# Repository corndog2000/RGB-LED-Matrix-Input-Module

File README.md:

# RGB-LED-Matrix-Input-Module

# Please check this project's license. It uses a Attribution-NonCommercial-ShareAlike 4.0 International license.

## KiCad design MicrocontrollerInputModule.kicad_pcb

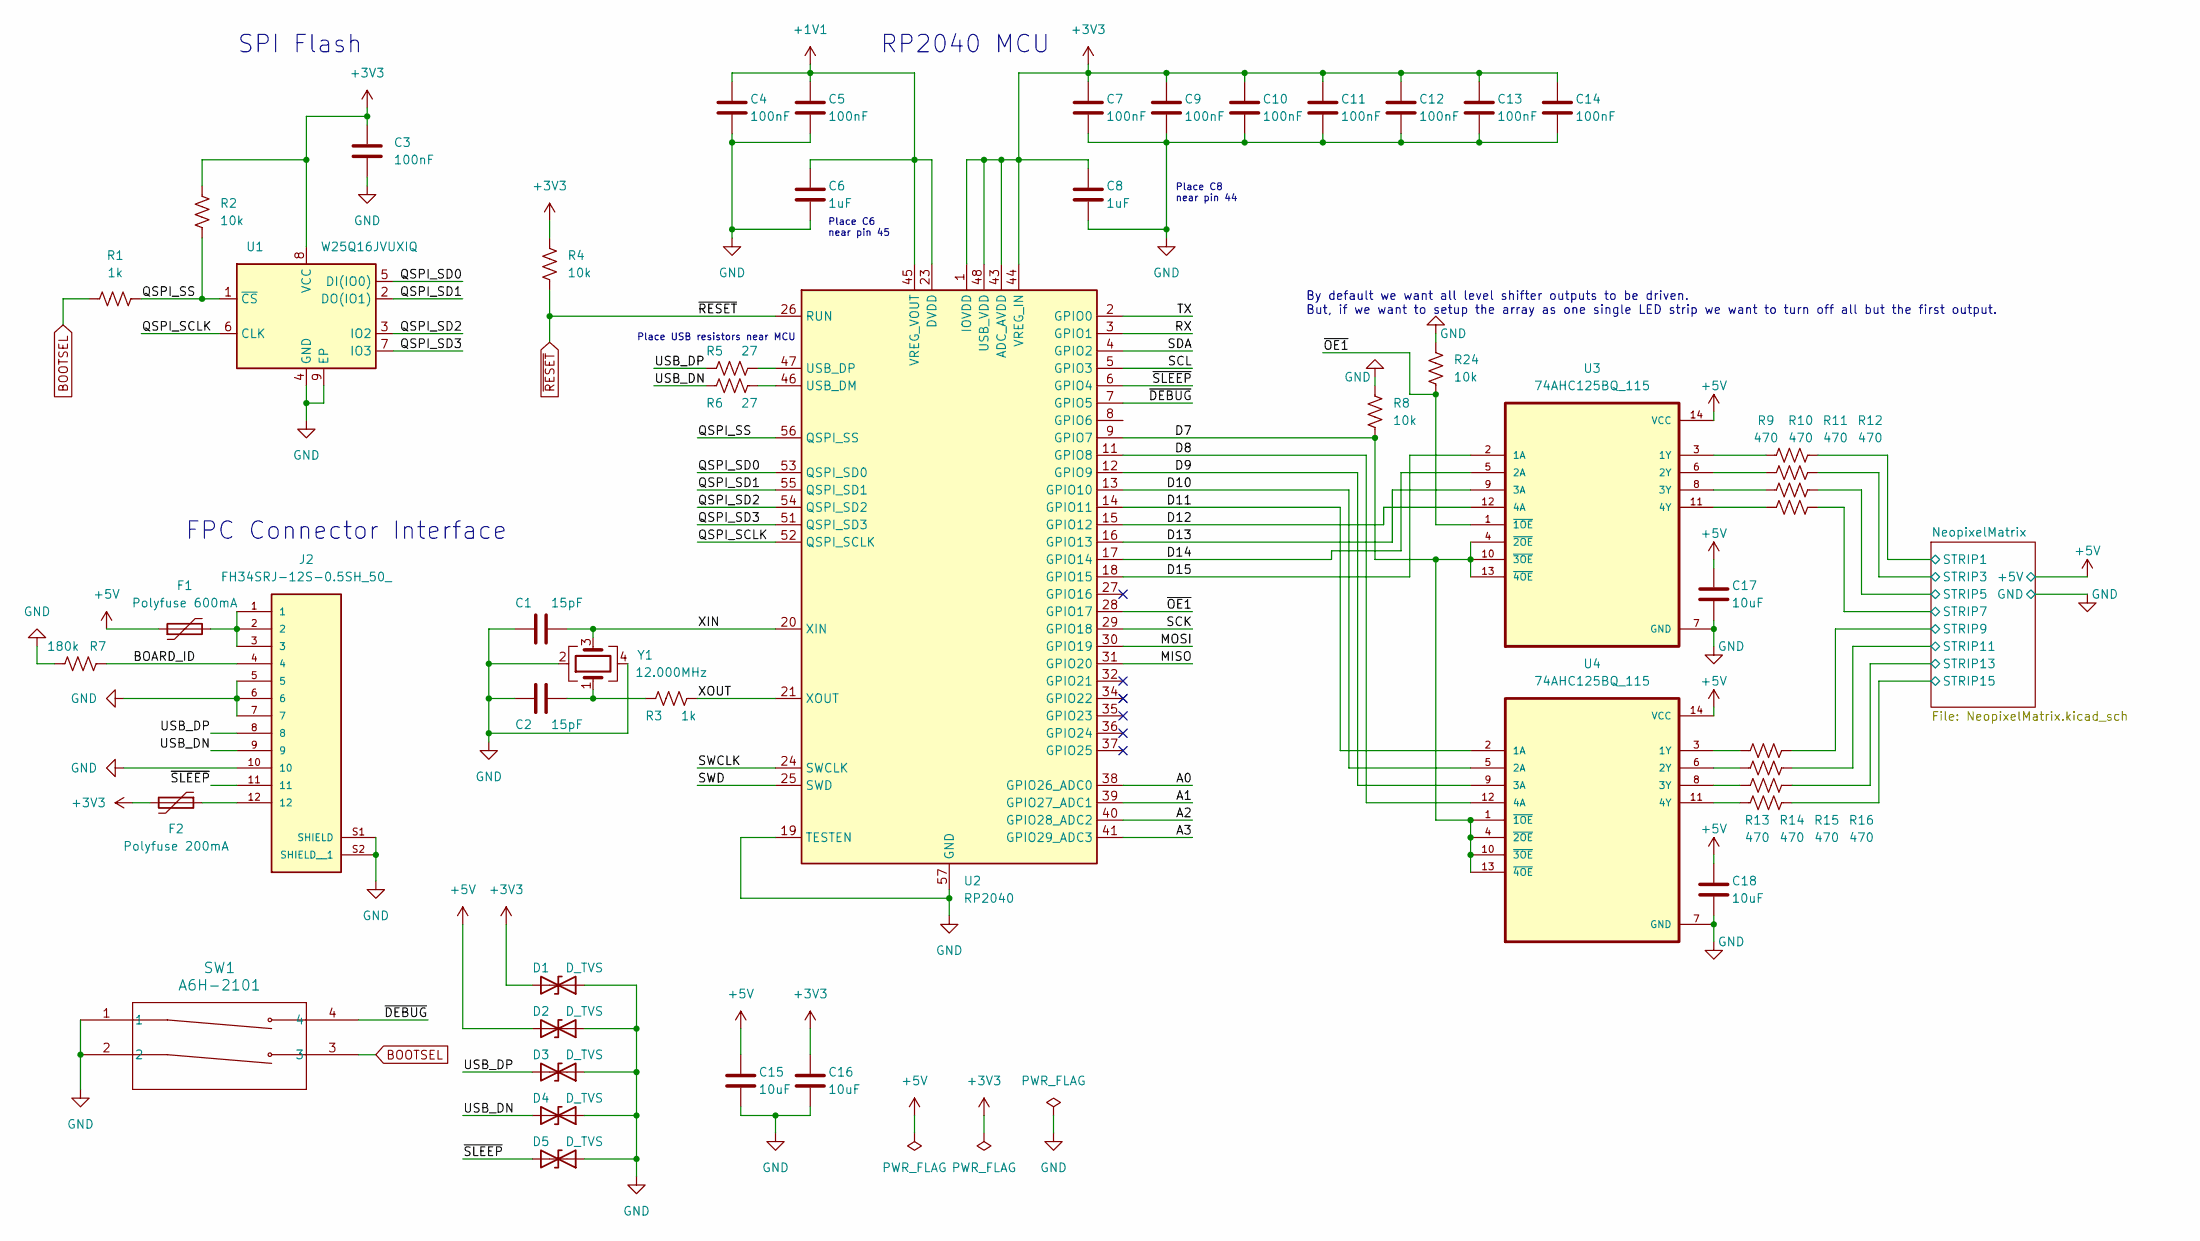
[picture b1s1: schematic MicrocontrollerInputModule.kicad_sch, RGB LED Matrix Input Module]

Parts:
C1, C2: 15pF; C_0402_1005Metric; LCSC Part # C76950
C3, C4, C5, C7, C9, C10, C11, C12, C13, C14: 100nF; C_0402_1005Metric; LCSC Part # C1525
C6, C8: 1uF; C_0402_1005Metric; LCSC Part # C29266
C15, C16, C17, C18: 10uF; C_0603_1608Metric; LCSC Part # C19702
D1, D2, D3, D4, D5: D_TVS; D_0402_1005Metric; LCSC Part # C468904
F1: Polyfuse 600mA; R_1206_3216Metric; LCSC Part # C883122
F2: Polyfuse 200mA; R_1206_3216Metric; LCSC Part # C910826
J2: FH34SRJ-12S-0.5SH_50_; HRS_FH34SRJ-12S-0.5SH_50_; LCSC Part # C424659
R1, R3: 1k; R_0402_1005Metric; LCSC Part # C106235
R2, R4, R8, R24: 10k; R_0402_1005Metric; LCSC Part # C60490
R5, R6: 27; R_0402_1005Metric; LCSC Part # C138021
R7: 180k; R_0402_1005Metric; LCSC Part # C138046
R9, R10, R11, R12, R13, R14, R15, R16: 470; R_0402_1005Metric; LCSC Part # C25117
SW1: A6H-2101; SW_A6H-2101_OMR; LCSC Part # C224990
U1: W25Q16JVUXIQ; SON-8-1EP_3x2mm_P0.5mm_EP0.2x1.6mm; LCSC Part # C2843335
U2: RP2040; QFN-56-1EP_7x7mm_P0.4mm_EP3.2x3.2mm; LCSC Part # C2040
U3, U4: 74AHC125BQ_115; QFN50P300X250X100-15N; LCSC Part # C554218
Y1: 12.000MHz; Crystal_SMD_3225-4Pin_3.2x2.5mm; LCSC Part # C7294551

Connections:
+1V1: C4.1, C5.1, C6.1, U2.23 (DVDD), U2.45 (VREG_VOUT), U2.50 (DVDD)
+3V3: C3.1, C7.1, C8.1, C9.1, C10.1, C11.1, C12.1, C13.1, C14.1, C16.1, D1.2 (A2), F2.2, R2.1, R4.1, U1.8 (VCC), U2.1 (IOVDD), U2.10 (IOVDD), U2.22 (IOVDD), U2.33 (IOVDD), U2.42 (IOVDD), U2.43 (ADC_AVDD), U2.44 (VREG_IN), U2.48 (USB_VDD), U2.49 (IOVDD)
+5V: C15.1, C17.1, C18.1, D2.2 (A2), F1.1, U3.14 (VCC), U4.14 (VCC); also elsewhere on the board
/A0: U2.38 (GPIO26_ADC0)
/A1: U2.39 (GPIO27_ADC1)
/A2: U2.40 (GPIO28_ADC2)
/A3: U2.41 (GPIO29_ADC3)
/BOARD_ID: J2.4, R7.1
/D7: R8.2, U2.9 (GPIO7), U3.4 (~2OE), U3.10 (~3OE), U3.13 (~4OE), U4.1 (~1OE), U4.4 (~2OE), U4.10 (~3OE), U4.13 (~4OE)
/D8: U2.11 (GPIO8), U4.12 (4A)
/D9: U2.12 (GPIO9), U4.9 (3A)
/D10: U2.13 (GPIO10), U4.5 (2A)
/D11: U2.14 (GPIO11), U4.2 (1A)
/D12: U2.15 (GPIO12), U3.12 (4A)
/D13: U2.16 (GPIO13), U3.9 (3A)
/D14: U2.17 (GPIO14), U3.5 (2A)
/D15: U2.18 (GPIO15), U3.2 (1A)
/MISO: U2.31 (GPIO20)
/MOSI: U2.30 (GPIO19)
/NeopixelMatrix/STRIP1: R9.2; also elsewhere on the board
/NeopixelMatrix/STRIP3: R10.2; also elsewhere on the board
/NeopixelMatrix/STRIP5: R11.2; also elsewhere on the board
/NeopixelMatrix/STRIP7: R12.2; also elsewhere on the board
/NeopixelMatrix/STRIP9: R13.2; also elsewhere on the board
/NeopixelMatrix/STRIP11: R14.2; also elsewhere on the board
/NeopixelMatrix/STRIP13: R15.2; also elsewhere on the board
/NeopixelMatrix/STRIP15: R16.2; also elsewhere on the board
/QSPI_SCLK: U1.6 (CLK), U2.52 (QSPI_SCLK)
/QSPI_SD0: U1.5 (DI(IO0)), U2.53 (QSPI_SD0)
/QSPI_SD1: U1.2 (DO(IO1)), U2.55 (QSPI_SD1)
/QSPI_SD2: U1.3 (IO2), U2.54 (QSPI_SD2)
/QSPI_SD3: U1.7 (IO3), U2.51 (QSPI_SD3)
/QSPI_SS: R1.2, R2.2, U1.1 (~CS), U2.56 (QSPI_SS)
/RX: U2.3 (GPIO1)
/SCK: U2.29 (GPIO18)
/SCL: U2.5 (GPIO3)
/SDA: U2.4 (GPIO2)
/SWCLK: U2.24 (SWCLK)
/SWD: U2.25 (SWD)
/TX: U2.2 (GPIO0)
/USB_DN: D4.2 (A2), J2.9, R6.1
/USB_DP: D3.2 (A2), J2.8, R5.1
/XIN: C1.2, U2.20 (XIN), Y1.3
/XOUT: R3.2, U2.21 (XOUT)
/~DEBUG: SW1.4, U2.7 (GPIO5)
/~OE1: R24.2, U2.28 (GPIO17), U3.1 (~1OE)
/~SLEEP: D5.2 (A2), J2.11, U2.6 (GPIO4)
BOOTSEL: R1.1, SW1.3
GND: C1.1, C2.1, C3.2, C4.2, C5.2, C6.2, C7.2, C8.2, C9.2, C10.2, C11.2, C12.2, C13.2, C14.2, C15.2, C16.2, C17.2, C18.2, D1.1 (A1), D2.1 (A1), D3.1 (A1), D4.1 (A1), D5.1 (A1), J2.5, J2.6, J2.7, J2.10, J2.S1 (SHIELD), J2.S2 (SHIELD__1), R7.2, R8.1, R24.1, SW1.1, SW1.2, U1.4 (GND), U1.9 (EP), U2.19 (TESTEN), U2.57 (GND), U3.7 (GND), U4.7 (GND), Y1.2, Y1.4; also elsewhere on the board
unnamed: C2.2, R3.1, Y1.1
unnamed: F1.2, J2.1, J2.2, J2.3
unnamed: F2.1, J2.12
unnamed: R6.2, U2.46 (USB_DM)
unnamed: R5.2, U2.47 (USB_DP)
unnamed: R9.1, U3.3 (1Y)
unnamed: R10.1, U3.6 (2Y)
unnamed: R11.1, U3.8 (3Y)
unnamed: R12.1, U3.11 (4Y)
unnamed: R13.1, U4.3 (1Y)
unnamed: R14.1, U4.6 (2Y)
unnamed: R15.1, U4.8 (3Y)
unnamed: R16.1, U4.11 (4Y)
~RESET: R4.2, U2.26 (RUN)

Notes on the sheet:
By default we want all level shifter outputs to be driven. But, if we want to setup the array as one single LED strip we want to turn off all but the first output.
SPI Flash
Place C8 near pin 44
Place USB resistors near MCU
Place C6 near pin 45
FPC Connector Interface
RP2040 MCU

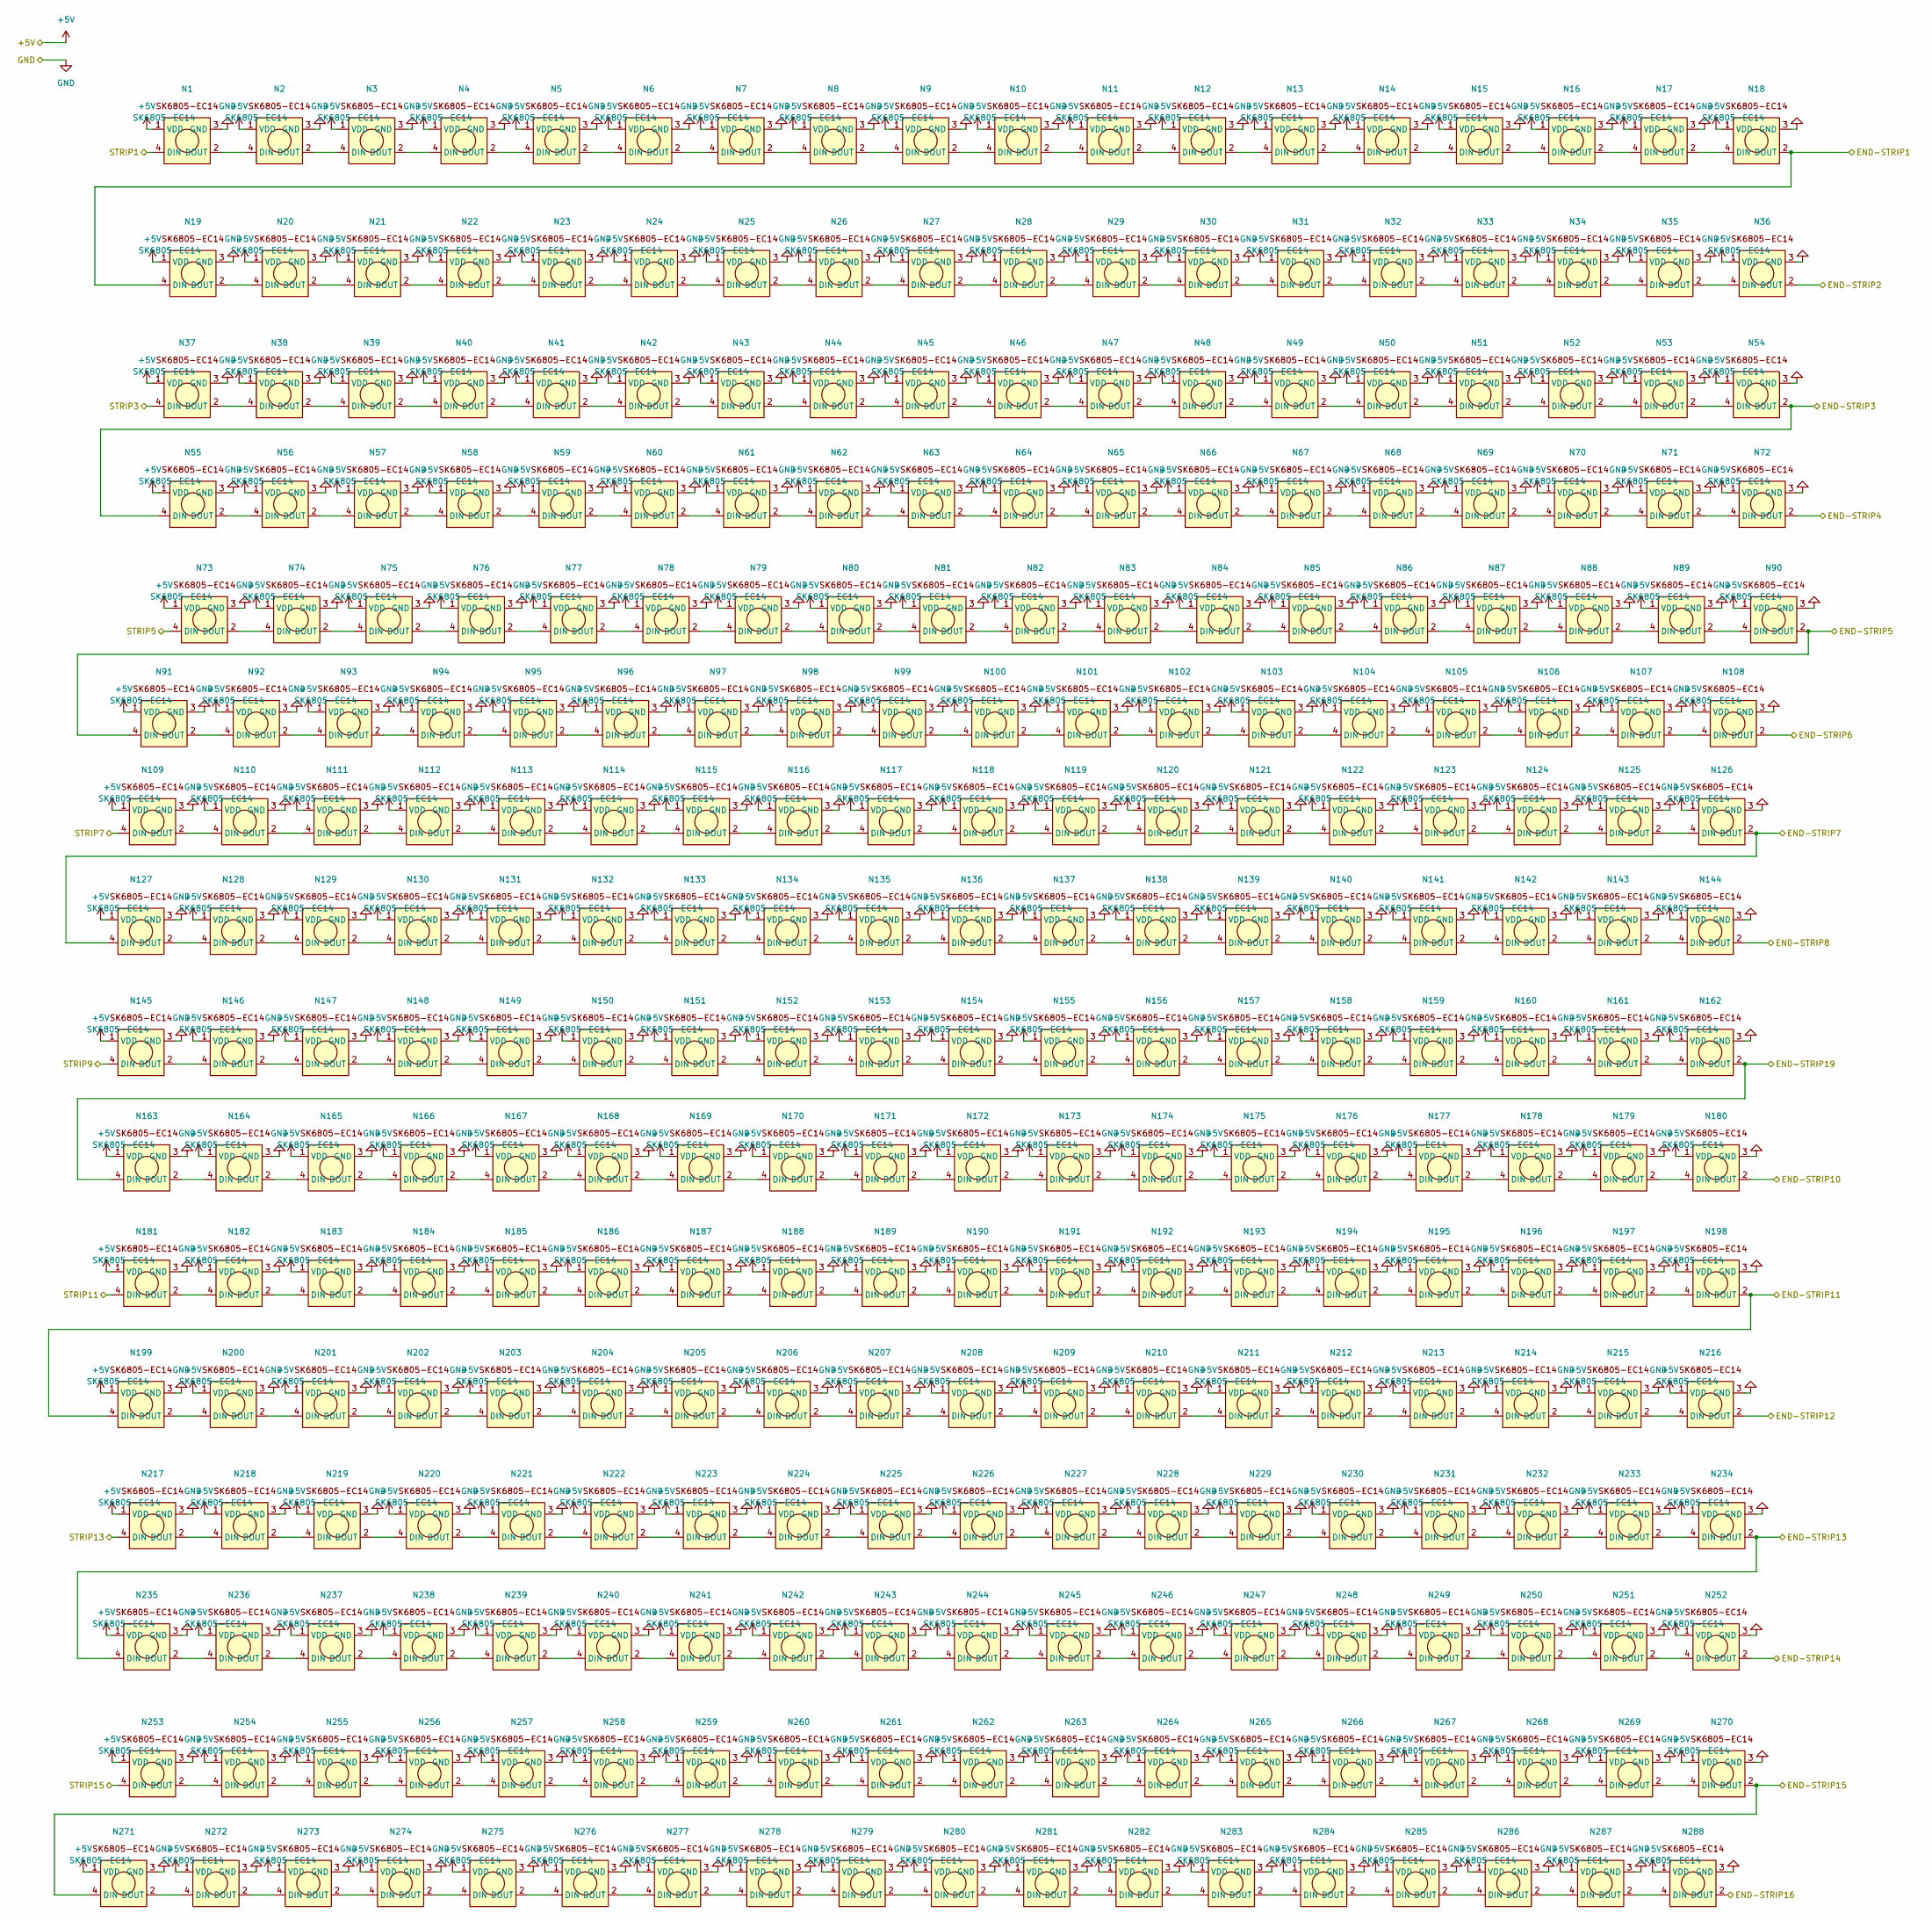
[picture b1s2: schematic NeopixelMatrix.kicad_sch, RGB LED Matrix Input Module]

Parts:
N1, N2, N3, N4, N5, N6, N7, N8, N9, N10, N11, N12, N13, N14, N15, N16, N17, N18, N19, N20, N21, N22, N23, N24, N25, N26, N27, N28, N29, N30, N31, N32, N33, N34, N35, N36, N37, N38, N39, N40, N41, N42, N43, N44, N45, N46, N47, N48, N49, N50, N51, N52, N53, N54, N55, N56, N57, N58, N59, N60, N61, N62, N63, N64, N65, N66, N67, N68, N69, N70, N71, N72, N73, N74, N75, N76, N77, N78, N79, N80, N81, N82, N83, N84, N85, N86, N87, N88, N89, N90, N91, N92, N93, N94, N95, N96, N97, N98, N99, N100, N101, N102, N103, N104, N105, N106, N107, N108, N109, N110, N111, N112, N113, N114, N115, N116, N117, N118, N119, N120, N121, N122, N123, N124, N125, N126, N127, N128, N129, N130, N131, N132, N133, N134, N135, N136, N137, N138, N139, N140, N141, N142, N143, N144, N145, N146, N147, N148, N149, N150, N151, N152, N153, N154, N155, N156, N157, N158, N159, N160, N161, N162, N163, N164, N165, N166, N167, N168, N169, N170, N171, N172, N173, N174, N175, N176, N177, N178, N179, N180, N181, N182, N183, N184, N185, N186, N187, N188, N189, N190, N191, N192, N193, N194, N195, N196, N197, N198, N199, N200, N201, N202, N203, N204, N205, N206, N207, N208, N209, N210, N211, N212, N213, N214, N215, N216, N217, N218, N219, N220, N221, N222, N223, N224, N225, N226, N227, N228, N229, N230, N231, N232, N233, N234, N235, N236, N237, N238, N239, N240, N241, N242, N243, N244, N245, N246, N247, N248, N249, N250, N251, N252, N253, N254, N255, N256, N257, N258, N259, N260, N261, N262, N263, N264, N265, N266, N267, N268, N269, N270, N271, N272, N273, N274, N275, N276, N277, N278, N279, N280, N281, N282, N283, N284, N285, N286, N287, N288: SK6805-EC14; LCSC Part # C2909055

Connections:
+5V: N1.1 (VDD), N2.1 (VDD), N3.1 (VDD), N4.1 (VDD), N5.1 (VDD), N6.1 (VDD), N7.1 (VDD), N8.1 (VDD), N9.1 (VDD), N10.1 (VDD), N11.1 (VDD), N12.1 (VDD), N13.1 (VDD), N14.1 (VDD), N15.1 (VDD), N16.1 (VDD), N17.1 (VDD), N18.1 (VDD), N19.1 (VDD), N20.1 (VDD), N21.1 (VDD), N22.1 (VDD), N23.1 (VDD), N24.1 (VDD), N25.1 (VDD), N26.1 (VDD), N27.1 (VDD), N28.1 (VDD), N29.1 (VDD), N30.1 (VDD), N31.1 (VDD), N32.1 (VDD), N33.1 (VDD), N34.1 (VDD), N35.1 (VDD), N36.1 (VDD), N37.1 (VDD), N38.1 (VDD), N39.1 (VDD), N40.1 (VDD), N41.1 (VDD), N42.1 (VDD), N43.1 (VDD), N44.1 (VDD), N45.1 (VDD), N46.1 (VDD), N47.1 (VDD), N48.1 (VDD), N49.1 (VDD), N50.1 (VDD), N51.1 (VDD), N52.1 (VDD), N53.1 (VDD), N54.1 (VDD), N55.1 (VDD), N56.1 (VDD), N57.1 (VDD), N58.1 (VDD), N59.1 (VDD), N60.1 (VDD), N61.1 (VDD), N62.1 (VDD), N63.1 (VDD), N64.1 (VDD), N65.1 (VDD), N66.1 (VDD), N67.1 (VDD), N68.1 (VDD), N69.1 (VDD), N70.1 (VDD), N71.1 (VDD), N72.1 (VDD), N73.1 (VDD), N74.1 (VDD), N75.1 (VDD), N76.1 (VDD), N77.1 (VDD), N78.1 (VDD), N79.1 (VDD), N80.1 (VDD), N81.1 (VDD), N82.1 (VDD), N83.1 (VDD), N84.1 (VDD), N85.1 (VDD), N86.1 (VDD), N87.1 (VDD), N88.1 (VDD), N89.1 (VDD), N90.1 (VDD), N91.1 (VDD), N92.1 (VDD), N93.1 (VDD), N94.1 (VDD), N95.1 (VDD), N96.1 (VDD), N97.1 (VDD), N98.1 (VDD), N99.1 (VDD), N100.1 (VDD), N101.1 (VDD), N102.1 (VDD), N103.1 (VDD), N104.1 (VDD), N105.1 (VDD), N106.1 (VDD), N107.1 (VDD), N108.1 (VDD), N109.1 (VDD), N110.1 (VDD), N111.1 (VDD), N112.1 (VDD), N113.1 (VDD), N114.1 (VDD), N115.1 (VDD), N116.1 (VDD), N117.1 (VDD), N118.1 (VDD), N119.1 (VDD), N120.1 (VDD), N121.1 (VDD), N122.1 (VDD), N123.1 (VDD), N124.1 (VDD), N125.1 (VDD), N126.1 (VDD), N127.1 (VDD), N128.1 (VDD), N129.1 (VDD), N130.1 (VDD), N131.1 (VDD), N132.1 (VDD), N133.1 (VDD), N134.1 (VDD), N135.1 (VDD), N136.1 (VDD), N137.1 (VDD), N138.1 (VDD), N139.1 (VDD), N140.1 (VDD), N141.1 (VDD), N142.1 (VDD), N143.1 (VDD), N144.1 (VDD), N145.1 (VDD), N146.1 (VDD), N147.1 (VDD), N148.1 (VDD), N149.1 (VDD), N150.1 (VDD), N151.1 (VDD), N152.1 (VDD), N153.1 (VDD), N154.1 (VDD), N155.1 (VDD), N156.1 (VDD), N157.1 (VDD), N158.1 (VDD), N159.1 (VDD), N160.1 (VDD), N161.1 (VDD), N162.1 (VDD), N163.1 (VDD), N164.1 (VDD), N165.1 (VDD), N166.1 (VDD), N167.1 (VDD), N168.1 (VDD), N169.1 (VDD), N170.1 (VDD), N171.1 (VDD), N172.1 (VDD), N173.1 (VDD), N174.1 (VDD), N175.1 (VDD), N176.1 (VDD), N177.1 (VDD), N178.1 (VDD), N179.1 (VDD), N180.1 (VDD), N181.1 (VDD), N182.1 (VDD), N183.1 (VDD), N184.1 (VDD), N185.1 (VDD), N186.1 (VDD), N187.1 (VDD), N188.1 (VDD), N189.1 (VDD), N190.1 (VDD), N191.1 (VDD), N192.1 (VDD), N193.1 (VDD), N194.1 (VDD), N195.1 (VDD), N196.1 (VDD), N197.1 (VDD), N198.1 (VDD), N199.1 (VDD), N200.1 (VDD), N201.1 (VDD), N202.1 (VDD), N203.1 (VDD), N204.1 (VDD), N205.1 (VDD), N206.1 (VDD), N207.1 (VDD), N208.1 (VDD), N209.1 (VDD), N210.1 (VDD), N211.1 (VDD), N212.1 (VDD), N213.1 (VDD), N214.1 (VDD), N215.1 (VDD), N216.1 (VDD), N217.1 (VDD), N218.1 (VDD), N219.1 (VDD), N220.1 (VDD), N221.1 (VDD), N222.1 (VDD), N223.1 (VDD), N224.1 (VDD), N225.1 (VDD), N226.1 (VDD), N227.1 (VDD), N228.1 (VDD), N229.1 (VDD), N230.1 (VDD), N231.1 (VDD), N232.1 (VDD), N233.1 (VDD), N234.1 (VDD), N235.1 (VDD), N236.1 (VDD), N237.1 (VDD), N238.1 (VDD), N239.1 (VDD), N240.1 (VDD), N241.1 (VDD), N242.1 (VDD), N243.1 (VDD), N244.1 (VDD), N245.1 (VDD), N246.1 (VDD), N247.1 (VDD), N248.1 (VDD), N249.1 (VDD), N250.1 (VDD), N251.1 (VDD), N252.1 (VDD), N253.1 (VDD), N254.1 (VDD), N255.1 (VDD), N256.1 (VDD), N257.1 (VDD), N258.1 (VDD), N259.1 (VDD), N260.1 (VDD), N261.1 (VDD), N262.1 (VDD), N263.1 (VDD), N264.1 (VDD), N265.1 (VDD), N266.1 (VDD), N267.1 (VDD), N268.1 (VDD), N269.1 (VDD), N270.1 (VDD), N271.1 (VDD), N272.1 (VDD), N273.1 (VDD), N274.1 (VDD), N275.1 (VDD), N276.1 (VDD), N277.1 (VDD), N278.1 (VDD), N279.1 (VDD), N280.1 (VDD), N281.1 (VDD), N282.1 (VDD), N283.1 (VDD), N284.1 (VDD), N285.1 (VDD), N286.1 (VDD), N287.1 (VDD), N288.1 (VDD); also elsewhere on the board
/NeopixelMatrix/END-STRIP1: N18.2 (DOUT), N19.4 (DIN)
/NeopixelMatrix/END-STRIP2: N36.2 (DOUT)
/NeopixelMatrix/END-STRIP3: N54.2 (DOUT), N55.4 (DIN)
/NeopixelMatrix/END-STRIP4: N72.2 (DOUT)
/NeopixelMatrix/END-STRIP5: N90.2 (DOUT), N91.4 (DIN)
/NeopixelMatrix/END-STRIP6: N108.2 (DOUT)
/NeopixelMatrix/END-STRIP7: N126.2 (DOUT), N127.4 (DIN)
/NeopixelMatrix/END-STRIP8: N144.2 (DOUT)
/NeopixelMatrix/END-STRIP10: N180.2 (DOUT)
/NeopixelMatrix/END-STRIP11: N198.2 (DOUT), N199.4 (DIN)
/NeopixelMatrix/END-STRIP12: N216.2 (DOUT)
/NeopixelMatrix/END-STRIP13: N234.2 (DOUT), N235.4 (DIN)
/NeopixelMatrix/END-STRIP14: N252.2 (DOUT)
/NeopixelMatrix/END-STRIP15: N270.2 (DOUT), N271.4 (DIN)
/NeopixelMatrix/END-STRIP16: N288.2 (DOUT)
/NeopixelMatrix/END-STRIP19: N162.2 (DOUT), N163.4 (DIN)
/NeopixelMatrix/STRIP1: N1.4 (DIN); also elsewhere on the board
/NeopixelMatrix/STRIP3: N37.4 (DIN); also elsewhere on the board
/NeopixelMatrix/STRIP5: N73.4 (DIN); also elsewhere on the board
/NeopixelMatrix/STRIP7: N109.4 (DIN); also elsewhere on the board
/NeopixelMatrix/STRIP9: N145.4 (DIN); also elsewhere on the board
/NeopixelMatrix/STRIP11: N181.4 (DIN); also elsewhere on the board
/NeopixelMatrix/STRIP13: N217.4 (DIN); also elsewhere on the board
/NeopixelMatrix/STRIP15: N253.4 (DIN); also elsewhere on the board
GND: N1.3 (GND), N2.3 (GND), N3.3 (GND), N4.3 (GND), N5.3 (GND), N6.3 (GND), N7.3 (GND), N8.3 (GND), N9.3 (GND), N10.3 (GND), N11.3 (GND), N12.3 (GND), N13.3 (GND), N14.3 (GND), N15.3 (GND), N16.3 (GND), N17.3 (GND), N18.3 (GND), N19.3 (GND), N20.3 (GND), N21.3 (GND), N22.3 (GND), N23.3 (GND), N24.3 (GND), N25.3 (GND), N26.3 (GND), N27.3 (GND), N28.3 (GND), N29.3 (GND), N30.3 (GND), N31.3 (GND), N32.3 (GND), N33.3 (GND), N34.3 (GND), N35.3 (GND), N36.3 (GND), N37.3 (GND), N38.3 (GND), N39.3 (GND), N40.3 (GND), N41.3 (GND), N42.3 (GND), N43.3 (GND), N44.3 (GND), N45.3 (GND), N46.3 (GND), N47.3 (GND), N48.3 (GND), N49.3 (GND), N50.3 (GND), N51.3 (GND), N52.3 (GND), N53.3 (GND), N54.3 (GND), N55.3 (GND), N56.3 (GND), N57.3 (GND), N58.3 (GND), N59.3 (GND), N60.3 (GND), N61.3 (GND), N62.3 (GND), N63.3 (GND), N64.3 (GND), N65.3 (GND), N66.3 (GND), N67.3 (GND), N68.3 (GND), N69.3 (GND), N70.3 (GND), N71.3 (GND), N72.3 (GND), N73.3 (GND), N74.3 (GND), N75.3 (GND), N76.3 (GND), N77.3 (GND), N78.3 (GND), N79.3 (GND), N80.3 (GND), N81.3 (GND), N82.3 (GND), N83.3 (GND), N84.3 (GND), N85.3 (GND), N86.3 (GND), N87.3 (GND), N88.3 (GND), N89.3 (GND), N90.3 (GND), N91.3 (GND), N92.3 (GND), N93.3 (GND), N94.3 (GND), N95.3 (GND), N96.3 (GND), N97.3 (GND), N98.3 (GND), N99.3 (GND), N100.3 (GND), N101.3 (GND), N102.3 (GND), N103.3 (GND), N104.3 (GND), N105.3 (GND), N106.3 (GND), N107.3 (GND), N108.3 (GND), N109.3 (GND), N110.3 (GND), N111.3 (GND), N112.3 (GND), N113.3 (GND), N114.3 (GND), N115.3 (GND), N116.3 (GND), N117.3 (GND), N118.3 (GND), N119.3 (GND), N120.3 (GND), N121.3 (GND), N122.3 (GND), N123.3 (GND), N124.3 (GND), N125.3 (GND), N126.3 (GND), N127.3 (GND), N128.3 (GND), N129.3 (GND), N130.3 (GND), N131.3 (GND), N132.3 (GND), N133.3 (GND), N134.3 (GND), N135.3 (GND), N136.3 (GND), N137.3 (GND), N138.3 (GND), N139.3 (GND), N140.3 (GND), N141.3 (GND), N142.3 (GND), N143.3 (GND), N144.3 (GND), N145.3 (GND), N146.3 (GND), N147.3 (GND), N148.3 (GND), N149.3 (GND), N150.3 (GND), N151.3 (GND), N152.3 (GND), N153.3 (GND), N154.3 (GND), N155.3 (GND), N156.3 (GND), N157.3 (GND), N158.3 (GND), N159.3 (GND), N160.3 (GND), N161.3 (GND), N162.3 (GND), N163.3 (GND), N164.3 (GND), N165.3 (GND), N166.3 (GND), N167.3 (GND), N168.3 (GND), N169.3 (GND), N170.3 (GND), N171.3 (GND), N172.3 (GND), N173.3 (GND), N174.3 (GND), N175.3 (GND), N176.3 (GND), N177.3 (GND), N178.3 (GND), N179.3 (GND), N180.3 (GND), N181.3 (GND), N182.3 (GND), N183.3 (GND), N184.3 (GND), N185.3 (GND), N186.3 (GND), N187.3 (GND), N188.3 (GND), N189.3 (GND), N190.3 (GND), N191.3 (GND), N192.3 (GND), N193.3 (GND), N194.3 (GND), N195.3 (GND), N196.3 (GND), N197.3 (GND), N198.3 (GND), N199.3 (GND), N200.3 (GND), N201.3 (GND), N202.3 (GND), N203.3 (GND), N204.3 (GND), N205.3 (GND), N206.3 (GND), N207.3 (GND), N208.3 (GND), N209.3 (GND), N210.3 (GND), N211.3 (GND), N212.3 (GND), N213.3 (GND), N214.3 (GND), N215.3 (GND), N216.3 (GND), N217.3 (GND), N218.3 (GND), N219.3 (GND), N220.3 (GND), N221.3 (GND), N222.3 (GND), N223.3 (GND), N224.3 (GND), N225.3 (GND), N226.3 (GND), N227.3 (GND), N228.3 (GND), N229.3 (GND), N230.3 (GND), N231.3 (GND), N232.3 (GND), N233.3 (GND), N234.3 (GND), N235.3 (GND), N236.3 (GND), N237.3 (GND), N238.3 (GND), N239.3 (GND), N240.3 (GND), N241.3 (GND), N242.3 (GND), N243.3 (GND), N244.3 (GND), N245.3 (GND), N246.3 (GND), N247.3 (GND), N248.3 (GND), N249.3 (GND), N250.3 (GND), N251.3 (GND), N252.3 (GND), N253.3 (GND), N254.3 (GND), N255.3 (GND), N256.3 (GND), N257.3 (GND), N258.3 (GND), N259.3 (GND), N260.3 (GND), N261.3 (GND), N262.3 (GND), N263.3 (GND), N264.3 (GND), N265.3 (GND), N266.3 (GND), N267.3 (GND), N268.3 (GND), N269.3 (GND), N270.3 (GND), N271.3 (GND), N272.3 (GND), N273.3 (GND), N274.3 (GND), N275.3 (GND), N276.3 (GND), N277.3 (GND), N278.3 (GND), N279.3 (GND), N280.3 (GND), N281.3 (GND), N282.3 (GND), N283.3 (GND), N284.3 (GND), N285.3 (GND), N286.3 (GND), N287.3 (GND), N288.3 (GND); also elsewhere on the board
unnamed: N1.2 (DOUT), N2.4 (DIN)
unnamed: N2.2 (DOUT), N3.4 (DIN)
unnamed: N3.2 (DOUT), N4.4 (DIN)
unnamed: N4.2 (DOUT), N5.4 (DIN)
unnamed: N5.2 (DOUT), N6.4 (DIN)
unnamed: N6.2 (DOUT), N7.4 (DIN)
unnamed: N7.2 (DOUT), N8.4 (DIN)
unnamed: N8.2 (DOUT), N9.4 (DIN)
unnamed: N9.2 (DOUT), N10.4 (DIN)
unnamed: N10.2 (DOUT), N11.4 (DIN)
unnamed: N11.2 (DOUT), N12.4 (DIN)
unnamed: N12.2 (DOUT), N13.4 (DIN)
unnamed: N13.2 (DOUT), N14.4 (DIN)
unnamed: N14.2 (DOUT), N15.4 (DIN)
unnamed: N15.2 (DOUT), N16.4 (DIN)
unnamed: N16.2 (DOUT), N17.4 (DIN)
unnamed: N17.2 (DOUT), N18.4 (DIN)
unnamed: N19.2 (DOUT), N20.4 (DIN)
unnamed: N20.2 (DOUT), N21.4 (DIN)
unnamed: N21.2 (DOUT), N22.4 (DIN)
unnamed: N22.2 (DOUT), N23.4 (DIN)
unnamed: N23.2 (DOUT), N24.4 (DIN)
unnamed: N24.2 (DOUT), N25.4 (DIN)
unnamed: N25.2 (DOUT), N26.4 (DIN)
unnamed: N26.2 (DOUT), N27.4 (DIN)
unnamed: N27.2 (DOUT), N28.4 (DIN)
unnamed: N28.2 (DOUT), N29.4 (DIN)
unnamed: N29.2 (DOUT), N30.4 (DIN)
unnamed: N30.2 (DOUT), N31.4 (DIN)
unnamed: N31.2 (DOUT), N32.4 (DIN)
unnamed: N32.2 (DOUT), N33.4 (DIN)
unnamed: N33.2 (DOUT), N34.4 (DIN)
unnamed: N34.2 (DOUT), N35.4 (DIN)
unnamed: N35.2 (DOUT), N36.4 (DIN)
unnamed: N37.2 (DOUT), N38.4 (DIN)
unnamed: N38.2 (DOUT), N39.4 (DIN)
unnamed: N39.2 (DOUT), N40.4 (DIN)
unnamed: N40.2 (DOUT), N41.4 (DIN)
unnamed: N41.2 (DOUT), N42.4 (DIN)
unnamed: N42.2 (DOUT), N43.4 (DIN)
unnamed: N43.2 (DOUT), N44.4 (DIN)
unnamed: N44.2 (DOUT), N45.4 (DIN)
unnamed: N45.2 (DOUT), N46.4 (DIN)
unnamed: N46.2 (DOUT), N47.4 (DIN)
unnamed: N47.2 (DOUT), N48.4 (DIN)
unnamed: N48.2 (DOUT), N49.4 (DIN)
unnamed: N49.2 (DOUT), N50.4 (DIN)
unnamed: N50.2 (DOUT), N51.4 (DIN)
unnamed: N51.2 (DOUT), N52.4 (DIN)
unnamed: N52.2 (DOUT), N53.4 (DIN)
unnamed: N53.2 (DOUT), N54.4 (DIN)
unnamed: N55.2 (DOUT), N56.4 (DIN)
unnamed: N56.2 (DOUT), N57.4 (DIN)
unnamed: N57.2 (DOUT), N58.4 (DIN)
unnamed: N58.2 (DOUT), N59.4 (DIN)
unnamed: N59.2 (DOUT), N60.4 (DIN)
unnamed: N60.2 (DOUT), N61.4 (DIN)
unnamed: N61.2 (DOUT), N62.4 (DIN)
unnamed: N62.2 (DOUT), N63.4 (DIN)
unnamed: N63.2 (DOUT), N64.4 (DIN)
unnamed: N64.2 (DOUT), N65.4 (DIN)
unnamed: N65.2 (DOUT), N66.4 (DIN)
unnamed: N66.2 (DOUT), N67.4 (DIN)
unnamed: N67.2 (DOUT), N68.4 (DIN)
unnamed: N68.2 (DOUT), N69.4 (DIN)
unnamed: N69.2 (DOUT), N70.4 (DIN)
unnamed: N70.2 (DOUT), N71.4 (DIN)
unnamed: N71.2 (DOUT), N72.4 (DIN)
unnamed: N73.2 (DOUT), N74.4 (DIN)
unnamed: N74.2 (DOUT), N75.4 (DIN)
unnamed: N75.2 (DOUT), N76.4 (DIN)
unnamed: N76.2 (DOUT), N77.4 (DIN)
unnamed: N77.2 (DOUT), N78.4 (DIN)
unnamed: N78.2 (DOUT), N79.4 (DIN)
unnamed: N79.2 (DOUT), N80.4 (DIN)
unnamed: N80.2 (DOUT), N81.4 (DIN)
unnamed: N81.2 (DOUT), N82.4 (DIN)
unnamed: N82.2 (DOUT), N83.4 (DIN)
unnamed: N83.2 (DOUT), N84.4 (DIN)
unnamed: N84.2 (DOUT), N85.4 (DIN)
unnamed: N85.2 (DOUT), N86.4 (DIN)
unnamed: N86.2 (DOUT), N87.4 (DIN)
unnamed: N87.2 (DOUT), N88.4 (DIN)
unnamed: N88.2 (DOUT), N89.4 (DIN)
unnamed: N89.2 (DOUT), N90.4 (DIN)
unnamed: N91.2 (DOUT), N92.4 (DIN)
unnamed: N92.2 (DOUT), N93.4 (DIN)
unnamed: N93.2 (DOUT), N94.4 (DIN)
unnamed: N94.2 (DOUT), N95.4 (DIN)
unnamed: N95.2 (DOUT), N96.4 (DIN)
unnamed: N96.2 (DOUT), N97.4 (DIN)
unnamed: N97.2 (DOUT), N98.4 (DIN)
unnamed: N98.2 (DOUT), N99.4 (DIN)
unnamed: N99.2 (DOUT), N100.4 (DIN)
unnamed: N100.2 (DOUT), N101.4 (DIN)
unnamed: N101.2 (DOUT), N102.4 (DIN)
unnamed: N102.2 (DOUT), N103.4 (DIN)
unnamed: N103.2 (DOUT), N104.4 (DIN)
unnamed: N104.2 (DOUT), N105.4 (DIN)
unnamed: N105.2 (DOUT), N106.4 (DIN)
unnamed: N106.2 (DOUT), N107.4 (DIN)
unnamed: N107.2 (DOUT), N108.4 (DIN)
unnamed: N109.2 (DOUT), N110.4 (DIN)
unnamed: N110.2 (DOUT), N111.4 (DIN)
unnamed: N111.2 (DOUT), N112.4 (DIN)
unnamed: N112.2 (DOUT), N113.4 (DIN)
unnamed: N113.2 (DOUT), N114.4 (DIN)
unnamed: N114.2 (DOUT), N115.4 (DIN)
unnamed: N115.2 (DOUT), N116.4 (DIN)
unnamed: N116.2 (DOUT), N117.4 (DIN)
unnamed: N117.2 (DOUT), N118.4 (DIN)
unnamed: N118.2 (DOUT), N119.4 (DIN)
unnamed: N119.2 (DOUT), N120.4 (DIN)
unnamed: N120.2 (DOUT), N121.4 (DIN)
unnamed: N121.2 (DOUT), N122.4 (DIN)
unnamed: N122.2 (DOUT), N123.4 (DIN)
unnamed: N123.2 (DOUT), N124.4 (DIN)
unnamed: N124.2 (DOUT), N125.4 (DIN)
unnamed: N125.2 (DOUT), N126.4 (DIN)
unnamed: N127.2 (DOUT), N128.4 (DIN)
unnamed: N128.2 (DOUT), N129.4 (DIN)
unnamed: N129.2 (DOUT), N130.4 (DIN)
unnamed: N130.2 (DOUT), N131.4 (DIN)
unnamed: N131.2 (DOUT), N132.4 (DIN)
unnamed: N132.2 (DOUT), N133.4 (DIN)
unnamed: N133.2 (DOUT), N134.4 (DIN)
unnamed: N134.2 (DOUT), N135.4 (DIN)
unnamed: N135.2 (DOUT), N136.4 (DIN)
unnamed: N136.2 (DOUT), N137.4 (DIN)
unnamed: N137.2 (DOUT), N138.4 (DIN)
unnamed: N138.2 (DOUT), N139.4 (DIN)
unnamed: N139.2 (DOUT), N140.4 (DIN)
unnamed: N140.2 (DOUT), N141.4 (DIN)
unnamed: N141.2 (DOUT), N142.4 (DIN)
unnamed: N142.2 (DOUT), N143.4 (DIN)
unnamed: N143.2 (DOUT), N144.4 (DIN)
unnamed: N145.2 (DOUT), N146.4 (DIN)
unnamed: N146.2 (DOUT), N147.4 (DIN)
unnamed: N147.2 (DOUT), N148.4 (DIN)
unnamed: N148.2 (DOUT), N149.4 (DIN)
unnamed: N149.2 (DOUT), N150.4 (DIN)
unnamed: N150.2 (DOUT), N151.4 (DIN)
unnamed: N151.2 (DOUT), N152.4 (DIN)
unnamed: N152.2 (DOUT), N153.4 (DIN)
unnamed: N153.2 (DOUT), N154.4 (DIN)
unnamed: N154.2 (DOUT), N155.4 (DIN)
unnamed: N155.2 (DOUT), N156.4 (DIN)
unnamed: N156.2 (DOUT), N157.4 (DIN)
unnamed: N157.2 (DOUT), N158.4 (DIN)
unnamed: N158.2 (DOUT), N159.4 (DIN)
unnamed: N159.2 (DOUT), N160.4 (DIN)
unnamed: N160.2 (DOUT), N161.4 (DIN)
unnamed: N161.2 (DOUT), N162.4 (DIN)
unnamed: N163.2 (DOUT), N164.4 (DIN)
unnamed: N164.2 (DOUT), N165.4 (DIN)
unnamed: N165.2 (DOUT), N166.4 (DIN)
unnamed: N166.2 (DOUT), N167.4 (DIN)
unnamed: N167.2 (DOUT), N168.4 (DIN)
unnamed: N168.2 (DOUT), N169.4 (DIN)
unnamed: N169.2 (DOUT), N170.4 (DIN)
unnamed: N170.2 (DOUT), N171.4 (DIN)
unnamed: N171.2 (DOUT), N172.4 (DIN)
unnamed: N172.2 (DOUT), N173.4 (DIN)
unnamed: N173.2 (DOUT), N174.4 (DIN)
unnamed: N174.2 (DOUT), N175.4 (DIN)
unnamed: N175.2 (DOUT), N176.4 (DIN)
unnamed: N176.2 (DOUT), N177.4 (DIN)
unnamed: N177.2 (DOUT), N178.4 (DIN)
unnamed: N178.2 (DOUT), N179.4 (DIN)
unnamed: N179.2 (DOUT), N180.4 (DIN)
unnamed: N181.2 (DOUT), N182.4 (DIN)
unnamed: N182.2 (DOUT), N183.4 (DIN)
unnamed: N183.2 (DOUT), N184.4 (DIN)
unnamed: N184.2 (DOUT), N185.4 (DIN)
unnamed: N185.2 (DOUT), N186.4 (DIN)
unnamed: N186.2 (DOUT), N187.4 (DIN)
unnamed: N187.2 (DOUT), N188.4 (DIN)
unnamed: N188.2 (DOUT), N189.4 (DIN)
unnamed: N189.2 (DOUT), N190.4 (DIN)
unnamed: N190.2 (DOUT), N191.4 (DIN)
unnamed: N191.2 (DOUT), N192.4 (DIN)
unnamed: N192.2 (DOUT), N193.4 (DIN)
unnamed: N193.2 (DOUT), N194.4 (DIN)
unnamed: N194.2 (DOUT), N195.4 (DIN)
unnamed: N195.2 (DOUT), N196.4 (DIN)
unnamed: N196.2 (DOUT), N197.4 (DIN)
unnamed: N197.2 (DOUT), N198.4 (DIN)
unnamed: N199.2 (DOUT), N200.4 (DIN)
unnamed: N200.2 (DOUT), N201.4 (DIN)
unnamed: N201.2 (DOUT), N202.4 (DIN)
unnamed: N202.2 (DOUT), N203.4 (DIN)
unnamed: N203.2 (DOUT), N204.4 (DIN)
unnamed: N204.2 (DOUT), N205.4 (DIN)
unnamed: N205.2 (DOUT), N206.4 (DIN)
unnamed: N206.2 (DOUT), N207.4 (DIN)
unnamed: N207.2 (DOUT), N208.4 (DIN)
unnamed: N208.2 (DOUT), N209.4 (DIN)
unnamed: N209.2 (DOUT), N210.4 (DIN)
unnamed: N210.2 (DOUT), N211.4 (DIN)
unnamed: N211.2 (DOUT), N212.4 (DIN)
unnamed: N212.2 (DOUT), N213.4 (DIN)
unnamed: N213.2 (DOUT), N214.4 (DIN)
unnamed: N214.2 (DOUT), N215.4 (DIN)
unnamed: N215.2 (DOUT), N216.4 (DIN)
unnamed: N217.2 (DOUT), N218.4 (DIN)
unnamed: N218.2 (DOUT), N219.4 (DIN)
unnamed: N219.2 (DOUT), N220.4 (DIN)
unnamed: N220.2 (DOUT), N221.4 (DIN)
unnamed: N221.2 (DOUT), N222.4 (DIN)
unnamed: N222.2 (DOUT), N223.4 (DIN)
unnamed: N223.2 (DOUT), N224.4 (DIN)
unnamed: N224.2 (DOUT), N225.4 (DIN)
unnamed: N225.2 (DOUT), N226.4 (DIN)
unnamed: N226.2 (DOUT), N227.4 (DIN)
unnamed: N227.2 (DOUT), N228.4 (DIN)
unnamed: N228.2 (DOUT), N229.4 (DIN)
unnamed: N229.2 (DOUT), N230.4 (DIN)
unnamed: N230.2 (DOUT), N231.4 (DIN)
unnamed: N231.2 (DOUT), N232.4 (DIN)
unnamed: N232.2 (DOUT), N233.4 (DIN)
unnamed: N233.2 (DOUT), N234.4 (DIN)
unnamed: N235.2 (DOUT), N236.4 (DIN)
unnamed: N236.2 (DOUT), N237.4 (DIN)
unnamed: N237.2 (DOUT), N238.4 (DIN)
unnamed: N238.2 (DOUT), N239.4 (DIN)
unnamed: N239.2 (DOUT), N240.4 (DIN)
unnamed: N240.2 (DOUT), N241.4 (DIN)
unnamed: N241.2 (DOUT), N242.4 (DIN)
unnamed: N242.2 (DOUT), N243.4 (DIN)
unnamed: N243.2 (DOUT), N244.4 (DIN)
unnamed: N244.2 (DOUT), N245.4 (DIN)
unnamed: N245.2 (DOUT), N246.4 (DIN)
unnamed: N246.2 (DOUT), N247.4 (DIN)
unnamed: N247.2 (DOUT), N248.4 (DIN)
unnamed: N248.2 (DOUT), N249.4 (DIN)
unnamed: N249.2 (DOUT), N250.4 (DIN)
unnamed: N250.2 (DOUT), N251.4 (DIN)
unnamed: N251.2 (DOUT), N252.4 (DIN)
unnamed: N253.2 (DOUT), N254.4 (DIN)
unnamed: N254.2 (DOUT), N255.4 (DIN)
unnamed: N255.2 (DOUT), N256.4 (DIN)
unnamed: N256.2 (DOUT), N257.4 (DIN)
unnamed: N257.2 (DOUT), N258.4 (DIN)
unnamed: N258.2 (DOUT), N259.4 (DIN)
unnamed: N259.2 (DOUT), N260.4 (DIN)
unnamed: N260.2 (DOUT), N261.4 (DIN)
unnamed: N261.2 (DOUT), N262.4 (DIN)
unnamed: N262.2 (DOUT), N263.4 (DIN)
unnamed: N263.2 (DOUT), N264.4 (DIN)
unnamed: N264.2 (DOUT), N265.4 (DIN)
unnamed: N265.2 (DOUT), N266.4 (DIN)
unnamed: N266.2 (DOUT), N267.4 (DIN)
unnamed: N267.2 (DOUT), N268.4 (DIN)
unnamed: N268.2 (DOUT), N269.4 (DIN)
unnamed: N269.2 (DOUT), N270.4 (DIN)
unnamed: N271.2 (DOUT), N272.4 (DIN)
unnamed: N272.2 (DOUT), N273.4 (DIN)
unnamed: N273.2 (DOUT), N274.4 (DIN)
unnamed: N274.2 (DOUT), N275.4 (DIN)
unnamed: N275.2 (DOUT), N276.4 (DIN)
unnamed: N276.2 (DOUT), N277.4 (DIN)
unnamed: N277.2 (DOUT), N278.4 (DIN)
unnamed: N278.2 (DOUT), N279.4 (DIN)
unnamed: N279.2 (DOUT), N280.4 (DIN)
unnamed: N280.2 (DOUT), N281.4 (DIN)
unnamed: N281.2 (DOUT), N282.4 (DIN)
unnamed: N282.2 (DOUT), N283.4 (DIN)
unnamed: N283.2 (DOUT), N284.4 (DIN)
unnamed: N284.2 (DOUT), N285.4 (DIN)
unnamed: N285.2 (DOUT), N286.4 (DIN)
unnamed: N286.2 (DOUT), N287.4 (DIN)
unnamed: N287.2 (DOUT), N288.4 (DIN)

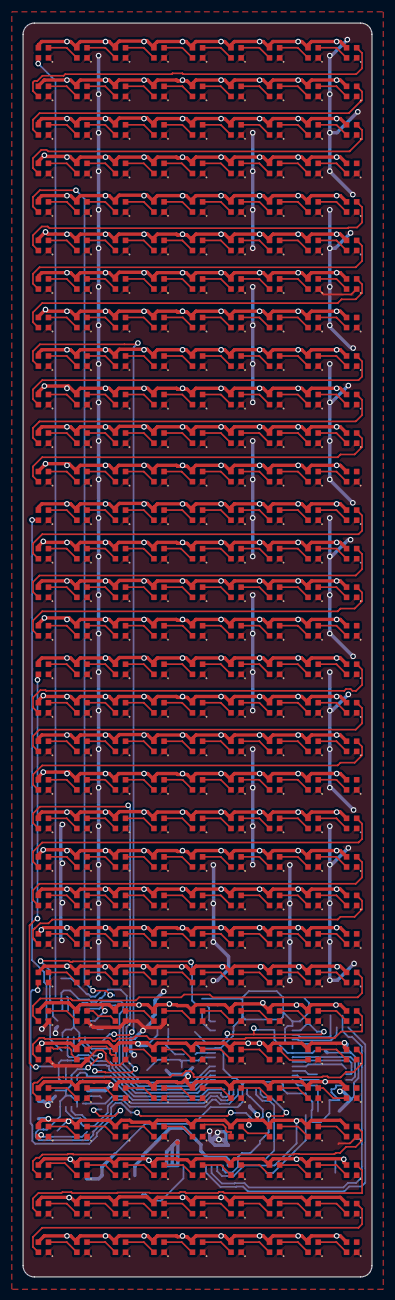
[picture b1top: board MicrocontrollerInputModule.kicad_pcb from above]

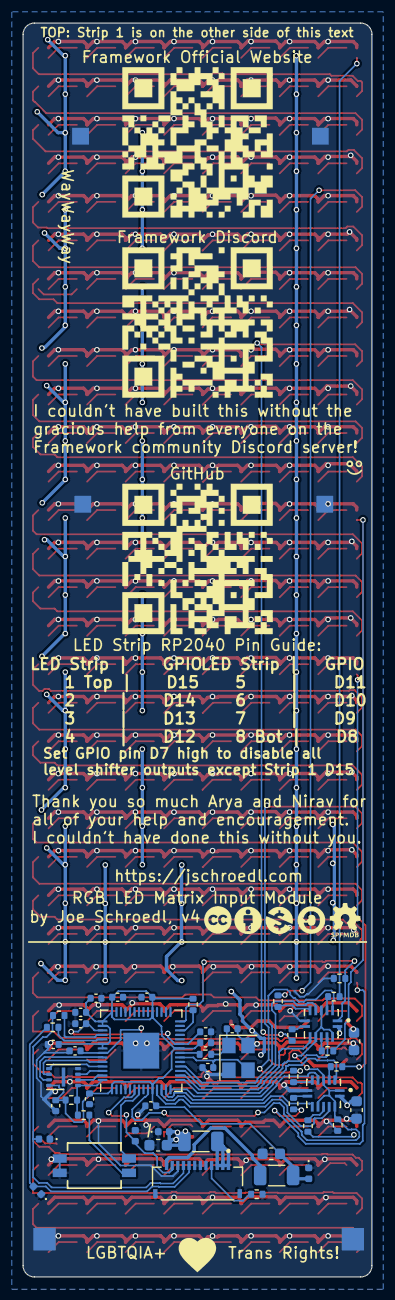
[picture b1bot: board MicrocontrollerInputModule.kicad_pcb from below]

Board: 2 copper layers, 31.0 x 111.4 mm, 337 parts (49 on the bottom side), 330 nets.

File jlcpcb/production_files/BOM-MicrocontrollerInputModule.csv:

Comment,Designator,Footprint,LCSC
1k,"R1,R3",R_0402_1005Metric,C106235
27,"R5,R6",R_0402_1005Metric,C138021
180k,R7,R_0402_1005Metric,C138046
100nF,"C10,C11,C12,C13,C14,C3,C4,C5,C7,C9",C_0402_1005Metric,C1525
10uF,"C15,C16,C17,C18",C_0603_1608Metric,C19702
RP2040,U2,QFN-56-1EP_7x7mm_P0.4mm_EP3.2x3.2mm,C2040
A6H-2101,SW1,SW_A6H-2101_OMR,C224990
470,"R10,R11,R12,R13,R14,R15,R16,R9",R_0402_1005Metric,C25117
W25Q16JVUXIQ ,U1,SON-8-1EP_3x2mm_P0.5mm_EP0.2x1.6mm,C2843335
SK6805-EC14,"N1,N10,N100,N101,N102,N103,N104,N105,N106,N107,N108,N109,N11,N110,N111,N112,N113,N114,N115,N116,N117,N118,N119,N12,N120,N121,N122,N123,N124,N125,N126,N127,N128,N129,N13,N130,N131,N132,N133,N134,N135,N136,N137,N138,N139,N14,N140,N141,N142,N143,N144,N145,N146,N147,N148,N149,N15,N150,N151,N152,N153,N154,N155,N156,N157,N158,N159,N16,N160,N161,N162,N163,N164,N165,N166,N167,N168,N169,N17,N170,N171,N172,N173,N174,N175,N176,N177,N178,N179,N18,N180,N181,N182,N183,N184,N185,N186,N187,N188,N189,N19,N190,N191,N192,N193,N194,N195,N196,N197,N198,N199,N2,N20,N200,N201,N202,N203,N204,N205,N206,N207,N208,N209,N21,N210,N211,N212,N213,N214,N215,N216,N217,N218,N219,N22,N220,N221,N222,N223,N224,N225,N226,N227,N228,N229,N23,N230,N231,N232,N233,N234,N235,N236,N237,N238,N239,N24,N240,N241,N242,N243,N244,N245,N246,N247,N248,N249,N25,N250,N251,N252,N253,N254,N255,N256,N257,N258,N259,N26,N260,N261,N262,N263,N264,N265,N266,N267,N268,N269,N27,N270,N271,N272,N273,N274,N275,N276,N277,N278,N279,N28,N280,N281,N282,N283,N284,N285,N286,N287,N288,N29,N3,N30,N31,N32,N33,N34,N35,N36,N37,N38,N39,N4,N40,N41,N42,N43,N44,N45,N46,N47,N48,N49,N5,N50,N51,N52,N53,N54,N55,N56,N57,N58,N59,N6,N60,N61,N62,N63,N64,N65,N66,N67,N68,N69,N7,N70,N71,N72,N73,N74,N75,N76,N77,N78,N79,N8,N80,N81,N82,N83,N84,N85,N86,N87,N88,N89,N9,N90,N91,N92,N93,N94,N95,N96,N97,N98,N99",SK6805-EC14,C2909055
1uF,"C6,C8",C_0402_1005Metric,C29266
FH34SRJ-12S-0.5SH_50_,J2,HRS_FH34SRJ-12S-0.5SH_50_,C424659
D_TVS,"D1,D2,D3,D4,D5",D_0402_1005Metric,C468904
74AHC125BQ_115,"U3,U4",QFN50P300X250X100-15N,C554218
10k,"R2,R24,R4,R8",R_0402_1005Metric,C60490
12.000MHz,Y1,Crystal_SMD_3225-4Pin_3.2x2.5mm,C7294551
15pF,"C1,C2",C_0402_1005Metric,C76950
Polyfuse 600mA,F1,R_1206_3216Metric,C883122
Polyfuse 200mA,F2,R_1206_3216Metric,C910826

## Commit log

2023-10-14 Version 2
2023-10-15 All traces ran. Zero DRC errors.
    Most of the DRC warnings can be ignored since they involve the LEDs and their footprints not including a certain layer or label.
2023-10-15 Fixed some routing issues for better Ground connections
2023-10-15 Added silkscreen
2023-10-15 PCB Assembly and Production Files
2023-10-21 Added dip switch
2023-10-22 Arya Edits and Feedback plus DIP Switch
2023-10-22 Adjusting silk screen and some wires
2023-10-22 Fabrication edits
2023-10-22 Added panelized kicad project folder
2023-10-22 Removed old gerber files
2024-04-01 V3 update in preparation for sale
2025-01-31 PCBway Shared Projects setup
2025-01-31 Updated PDF
